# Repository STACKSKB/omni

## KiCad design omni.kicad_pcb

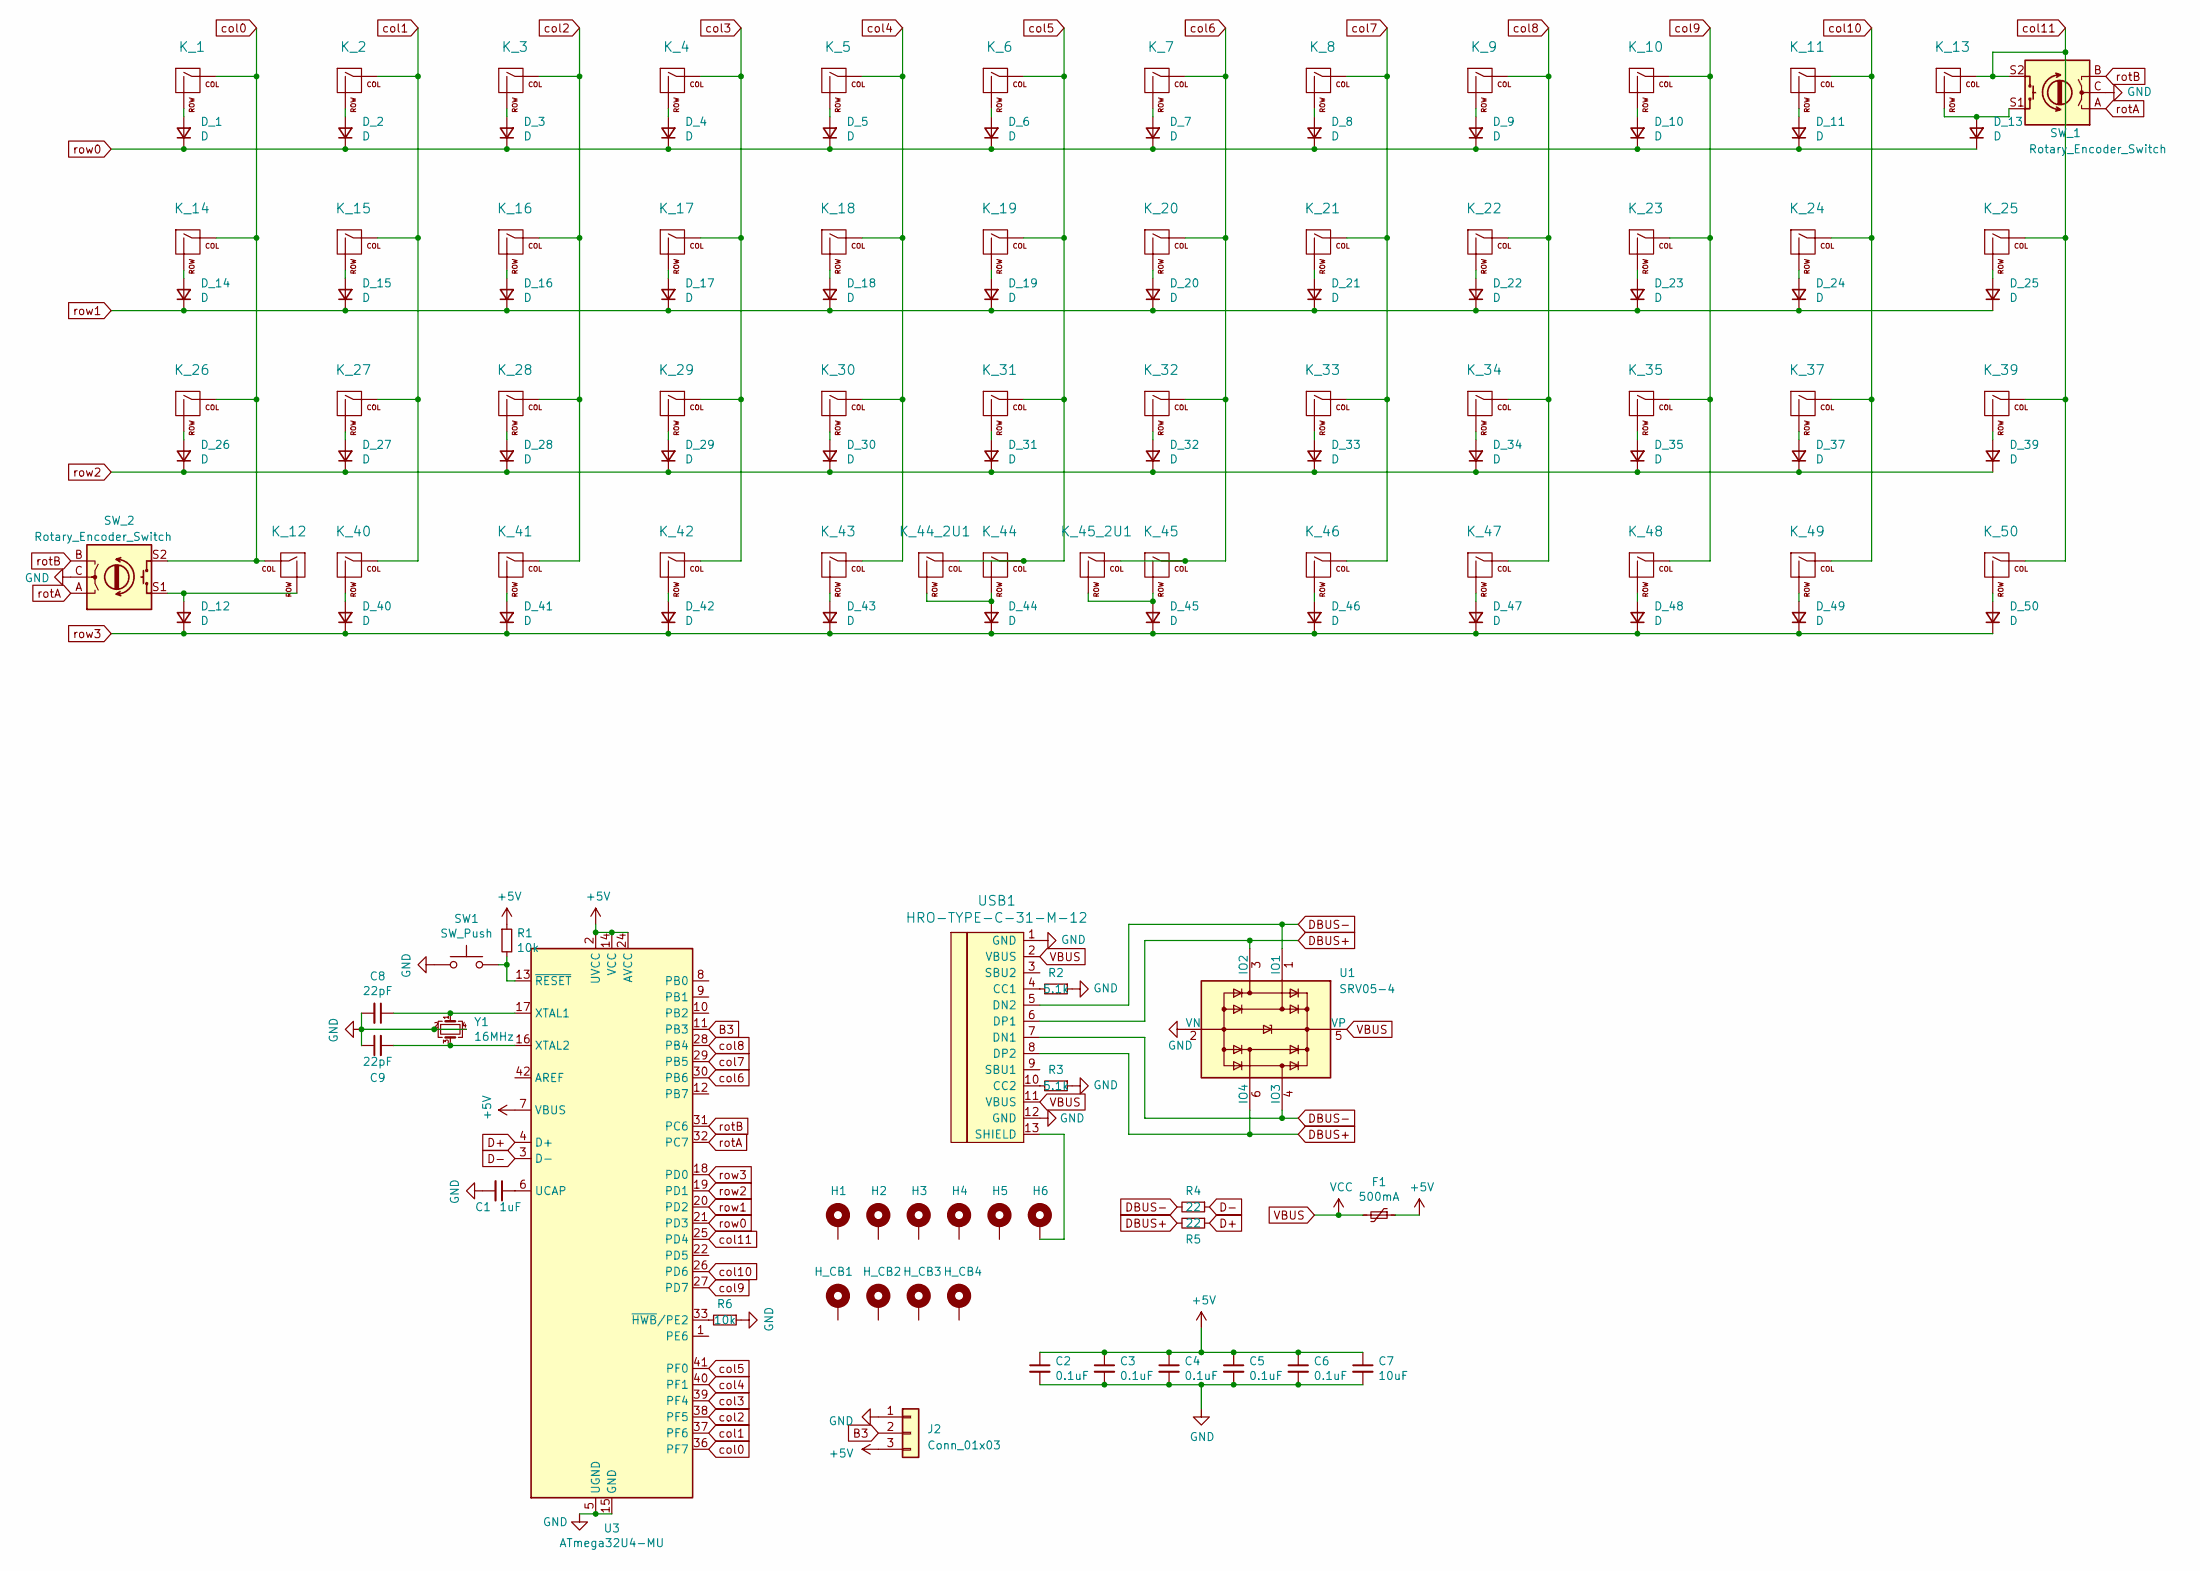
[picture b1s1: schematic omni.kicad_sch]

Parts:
C1: 1uF; C_0603_1608Metric
C2, C3, C4, C5, C6: 0.1uF; C_0603_1608Metric
C7: 10uF; C_0603_1608Metric
C8, C9: 22pF; C_0603_1608Metric
D_1, D_2, D_3, D_4, D_5, D_6, D_7, D_8, D_9, D_10, D_11, D_12, D_13, D_14, D_15, D_16, D_17, D_18, D_19, D_20, D_21, D_22, D_23, D_24, D_25, D_26, D_27, D_28, D_29, D_30, D_31, D_32, D_33, D_34, D_35, D_37, D_39, D_40, D_41, D_42, D_43, D_44, D_45, D_46, D_47, D_48, D_49, D_50: D; D_SOD-123
F1: 500mA; Fuse_1206_3216Metric
H1, H2, H3, H4, H5, H6: MountingHole_Pad; MountingHole_2.2mm_M2_Pad
H_CB1, H_CB2, H_CB3, H_CB4: MountingHole_Pad; MountingHole_2.2mm_M2_Pad
J2: Conn_01x03; StripLED_front
K_1, K_2, K_3, K_4, K_5, K_6, K_7, K_8, K_9, K_10, K_11, K_12, K_13, K_14, K_15, K_16, K_17, K_18, K_19, K_20, K_21, K_22, K_23, K_24, K_25, K_26, K_27, K_28, K_29, K_30, K_31, K_32, K_33, K_34, K_35, K_37, K_39, K_40, K_41, K_42, K_43, K_44, K_45, K_46, K_47, K_48, K_49, K_50: KEYSW; MXOnly-1U-NoLED
K_44_2U1, K_45_2U1: KEYSW; MXOnly-2U-ReversedStabilizers-NoLED
R1, R6: 10k; R_0603_1608Metric
R2, R3: 5.1k; R_0603_1608Metric
R4, R5: 22; R_0603_1608Metric
SW1: SW_Push; SW_Push_SPST_NO_Alps_SKRK
SW_1, SW_2: Rotary_Encoder_Switch; RotaryEncoder_Alps_EC11E-Switch_Vertical_H20mm
U1: SRV05-4; SOT-23-6
U3: ATmega32U4-MU; QFN-44-1EP_7x7mm_P0.5mm_EP5.2x5.2mm
USB1: HRO-TYPE-C-31-M-12; HRO-TYPE-C-31-M-12-Assembly
Y1: 16MHz; Crystal_SMD_3225-4Pin_3.2x2.5mm

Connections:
+5V: C2.1, C3.1, C4.1, C5.1, C6.1, C7.1, F1.1, J2.3, R1.1, U3.2 (UVCC), U3.7 (VBUS), U3.14 (VCC), U3.24 (AVCC), U3.34 (VCC), U3.44 (AVCC)
B3: J2.2, U3.11 (PB3)
D+: R5.1, U3.4 (D+)
D-: R4.1, U3.3 (D-)
DBUS+: R5.2, U1.3 (IO2), U1.6 (IO4), USB1.6 (DP1), USB1.8 (DP2)
DBUS-: R4.2, U1.1 (IO1), U1.4 (IO3), USB1.5 (DN2), USB1.7 (DN1)
GND: C1.2, C2.2, C3.2, C4.2, C5.2, C6.2, C7.2, C8.2, C9.1, J2.1, R2.1, R3.1, R6.1, SW1.1, SW_1.C, SW_2.C, U1.2 (VN), U3.5 (UGND), U3.15 (GND), U3.23 (GND), U3.35 (GND), U3.43 (GND), U3.45 (GND), USB1.1 (GND), USB1.12 (GND), Y1.2, Y1.4
unnamed: D_1.2 (A), K_1.2 (ROW)
unnamed: D_2.2 (A), K_2.2 (ROW)
unnamed: D_3.2 (A), K_3.2 (ROW)
unnamed: D_4.2 (A), K_4.2 (ROW)
unnamed: D_5.2 (A), K_5.2 (ROW)
unnamed: D_6.2 (A), K_6.2 (ROW)
unnamed: D_7.2 (A), K_7.2 (ROW)
unnamed: D_8.2 (A), K_8.2 (ROW)
unnamed: D_9.2 (A), K_9.2 (ROW)
unnamed: D_10.2 (A), K_10.2 (ROW)
unnamed: D_11.2 (A), K_11.2 (ROW)
unnamed: D_12.2 (A), K_12.2 (ROW), SW_2.S1
unnamed: D_13.2 (A), K_13.2 (ROW), SW_1.S1
unnamed: D_14.2 (A), K_14.2 (ROW)
unnamed: D_15.2 (A), K_15.2 (ROW)
unnamed: D_16.2 (A), K_16.2 (ROW)
unnamed: D_17.2 (A), K_17.2 (ROW)
unnamed: D_18.2 (A), K_18.2 (ROW)
unnamed: D_19.2 (A), K_19.2 (ROW)
unnamed: D_20.2 (A), K_20.2 (ROW)
unnamed: D_21.2 (A), K_21.2 (ROW)
unnamed: D_22.2 (A), K_22.2 (ROW)
unnamed: D_23.2 (A), K_23.2 (ROW)
unnamed: D_24.2 (A), K_24.2 (ROW)
unnamed: D_25.2 (A), K_25.2 (ROW)
unnamed: D_26.2 (A), K_26.2 (ROW)
unnamed: D_27.2 (A), K_27.2 (ROW)
unnamed: D_28.2 (A), K_28.2 (ROW)
unnamed: D_29.2 (A), K_29.2 (ROW)
unnamed: D_30.2 (A), K_30.2 (ROW)
unnamed: D_31.2 (A), K_31.2 (ROW)
unnamed: D_32.2 (A), K_32.2 (ROW)
unnamed: D_33.2 (A), K_33.2 (ROW)
unnamed: D_34.2 (A), K_34.2 (ROW)
unnamed: D_35.2 (A), K_35.2 (ROW)
unnamed: D_37.2 (A), K_37.2 (ROW)
unnamed: D_39.2 (A), K_39.2 (ROW)
unnamed: D_40.2 (A), K_40.2 (ROW)
unnamed: D_41.2 (A), K_41.2 (ROW)
unnamed: D_42.2 (A), K_42.2 (ROW)
unnamed: D_43.2 (A), K_43.2 (ROW)
unnamed: D_44.2 (A), K_44.2 (ROW), K_44_2U1.2 (ROW)
unnamed: D_45.2 (A), K_45.2 (ROW), K_45_2U1.2 (ROW)
unnamed: D_46.2 (A), K_46.2 (ROW)
unnamed: D_47.2 (A), K_47.2 (ROW)
unnamed: D_48.2 (A), K_48.2 (ROW)
unnamed: D_49.2 (A), K_49.2 (ROW)
unnamed: D_50.2 (A), K_50.2 (ROW)
unnamed: C1.1, U3.6 (UCAP)
unnamed: C8.1, U3.17 (XTAL1), Y1.1
unnamed: C9.2, U3.16 (XTAL2), Y1.3
unnamed: R6.2, U3.33 (~HWB/PE2)
unnamed: R1.2, SW1.2, U3.13 (~RESET)
unnamed: R2.2, USB1.4 (CC1)
unnamed: R3.2, USB1.10 (CC2)
unnamed: H6.1, USB1.13 (SHIELD)
VBUS: F1.2, U1.5 (VP), USB1.2 (VBUS), USB1.11 (VBUS)
col0: K_1.1 (COL), K_12.1 (COL), K_14.1 (COL), K_26.1 (COL), SW_2.S2, U3.36 (PF7)
col1: K_2.1 (COL), K_15.1 (COL), K_27.1 (COL), K_40.1 (COL), U3.37 (PF6)
col2: K_3.1 (COL), K_16.1 (COL), K_28.1 (COL), K_41.1 (COL), U3.38 (PF5)
col3: K_4.1 (COL), K_17.1 (COL), K_29.1 (COL), K_42.1 (COL), U3.39 (PF4)
col4: K_5.1 (COL), K_18.1 (COL), K_30.1 (COL), K_43.1 (COL), U3.40 (PF1)
col5: K_6.1 (COL), K_19.1 (COL), K_31.1 (COL), K_44.1 (COL), K_44_2U1.1 (COL), U3.41 (PF0)
col6: K_7.1 (COL), K_20.1 (COL), K_32.1 (COL), K_45.1 (COL), K_45_2U1.1 (COL), U3.30 (PB6)
col7: K_8.1 (COL), K_21.1 (COL), K_33.1 (COL), K_46.1 (COL), U3.29 (PB5)
col8: K_9.1 (COL), K_22.1 (COL), K_34.1 (COL), K_47.1 (COL), U3.28 (PB4)
col9: K_10.1 (COL), K_23.1 (COL), K_35.1 (COL), K_48.1 (COL), U3.27 (PD7)
col10: K_11.1 (COL), K_24.1 (COL), K_37.1 (COL), K_49.1 (COL), U3.26 (PD6)
col11: K_13.1 (COL), K_25.1 (COL), K_39.1 (COL), K_50.1 (COL), SW_1.S2, U3.25 (PD4)
rotA: SW_1.A, SW_2.A, U3.32 (PC7)
rotB: SW_1.B, SW_2.B, U3.31 (PC6)
row0: D_1.1 (K), D_2.1 (K), D_3.1 (K), D_4.1 (K), D_5.1 (K), D_6.1 (K), D_7.1 (K), D_8.1 (K), D_9.1 (K), D_10.1 (K), D_11.1 (K), D_13.1 (K), U3.21 (PD3)
row1: D_14.1 (K), D_15.1 (K), D_16.1 (K), D_17.1 (K), D_18.1 (K), D_19.1 (K), D_20.1 (K), D_21.1 (K), D_22.1 (K), D_23.1 (K), D_24.1 (K), D_25.1 (K), U3.20 (PD2)
row2: D_26.1 (K), D_27.1 (K), D_28.1 (K), D_29.1 (K), D_30.1 (K), D_31.1 (K), D_32.1 (K), D_33.1 (K), D_34.1 (K), D_35.1 (K), D_37.1 (K), D_39.1 (K), U3.19 (PD1)
row3: D_12.1 (K), D_40.1 (K), D_41.1 (K), D_42.1 (K), D_43.1 (K), D_44.1 (K), D_45.1 (K), D_46.1 (K), D_47.1 (K), D_48.1 (K), D_49.1 (K), D_50.1 (K), U3.18 (PD0)

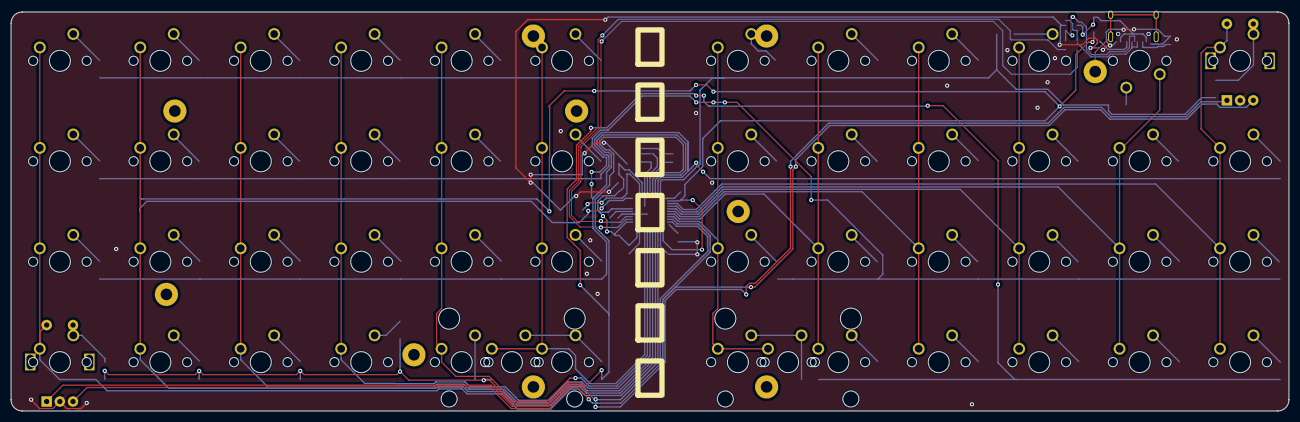
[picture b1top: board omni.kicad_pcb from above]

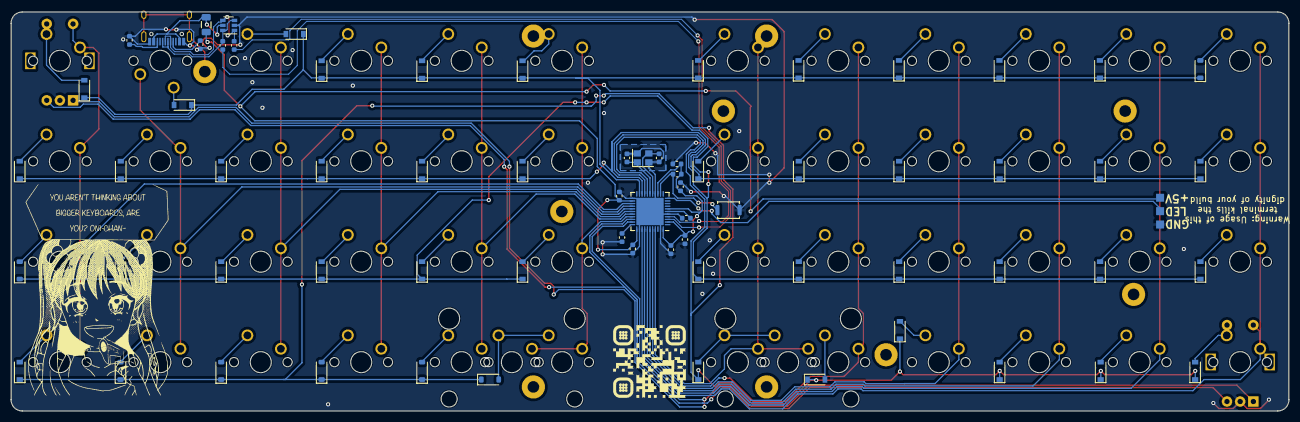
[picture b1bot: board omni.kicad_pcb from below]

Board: 2 copper layers, 242.4 x 75.7 mm, 132 parts (70 on the bottom side), 82 nets.
